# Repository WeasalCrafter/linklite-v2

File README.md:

<!-- PROJECT LOGO -->
<br />
<div align="center">

  <h3 align="center">LinkLite v2</h3>

  <p align="center">
    A modular ESP32-C6 based room light that syncs brightness via ESP-NOW
    <br />
    <a href="https://www.loganfick.com/projects/linklite-v2">See my post on my Website</a><!--
    &middot;
    <a href="#">Project video on Youtube</a>-->
  </p>
</div>

<!-- TABLE OF CONTENTS -->
<details opeb>
  <summary>Table of Contents</summary>
  <ol>
    <li>
      <a href="#files">File Structure</a>
    <li><a href="#contact">Contact</a></li>
    <li><a href="#acknowledgments">Acknowledgments</a></li>
    <li><a href="#license">License</a></li>
  </ol>
</details>

<!-- ABOUT THE PROJECT -->
## About The Project

My dorm room lights are terrible in college, so I decided to make my own. LinkLite is the idea of a modular lighting system that lives locally and not in the cloud while allowing for wireless control and syncing. 

This is the second version of LinkLite, completely redesigned. This time with a custom PCB and much increased brightness.

### Built With

These are the major libraries I used in the programming in the project:

* RotaryEncoder
* Preferences
* ESP-NOW

<!-- CONTACT -->
## Files

The PCB project files can be found under ```kicad/linklite_v2```

```
linklite-v2
├── data
├── kicad
│   └── linklite_v2
├── linklite-bar
├── linklite-controller
├── temperature_logger
├── README.md
├── CLAUDE.md
└── LICENSE.txt
```

The arduino sketches for the ```linklite-bar```, ```linklite-controller```, and ```temperature_logger``` can be found under their respective folders, and my data collected can be found in the ```data``` folder along with the MATLAB script for plot generation.

<!-- CONTACT -->
## Contact

Logan Fick -  loganfickcontact@gmail.com

Project Link: [https://github.com/weasalcrafter/linklite-v2](https://github.com/weasalcrafter/linklite-v2)

Website: [https://loganfick.com/](https://loganfick.com/)

<!-- ACKNOWLEDGMENTS -->
## Acknowledgments
These are the tools I used for this project for designing the schematic, PCB layout, and programming.

* [Claude Code](https://www.claude.ai)
* [KiCad 10.0](https://www.kicad.org/)
* [Digikey Tools](https://www.digikey.com/en/resources/online-conversion-calculators)
* [MATLAB](https://www.mathworks.com/products/matlab.html)

## License

This project is licensed under the MIT License - see the [LICENSE](LICENSE.txt) file for details.

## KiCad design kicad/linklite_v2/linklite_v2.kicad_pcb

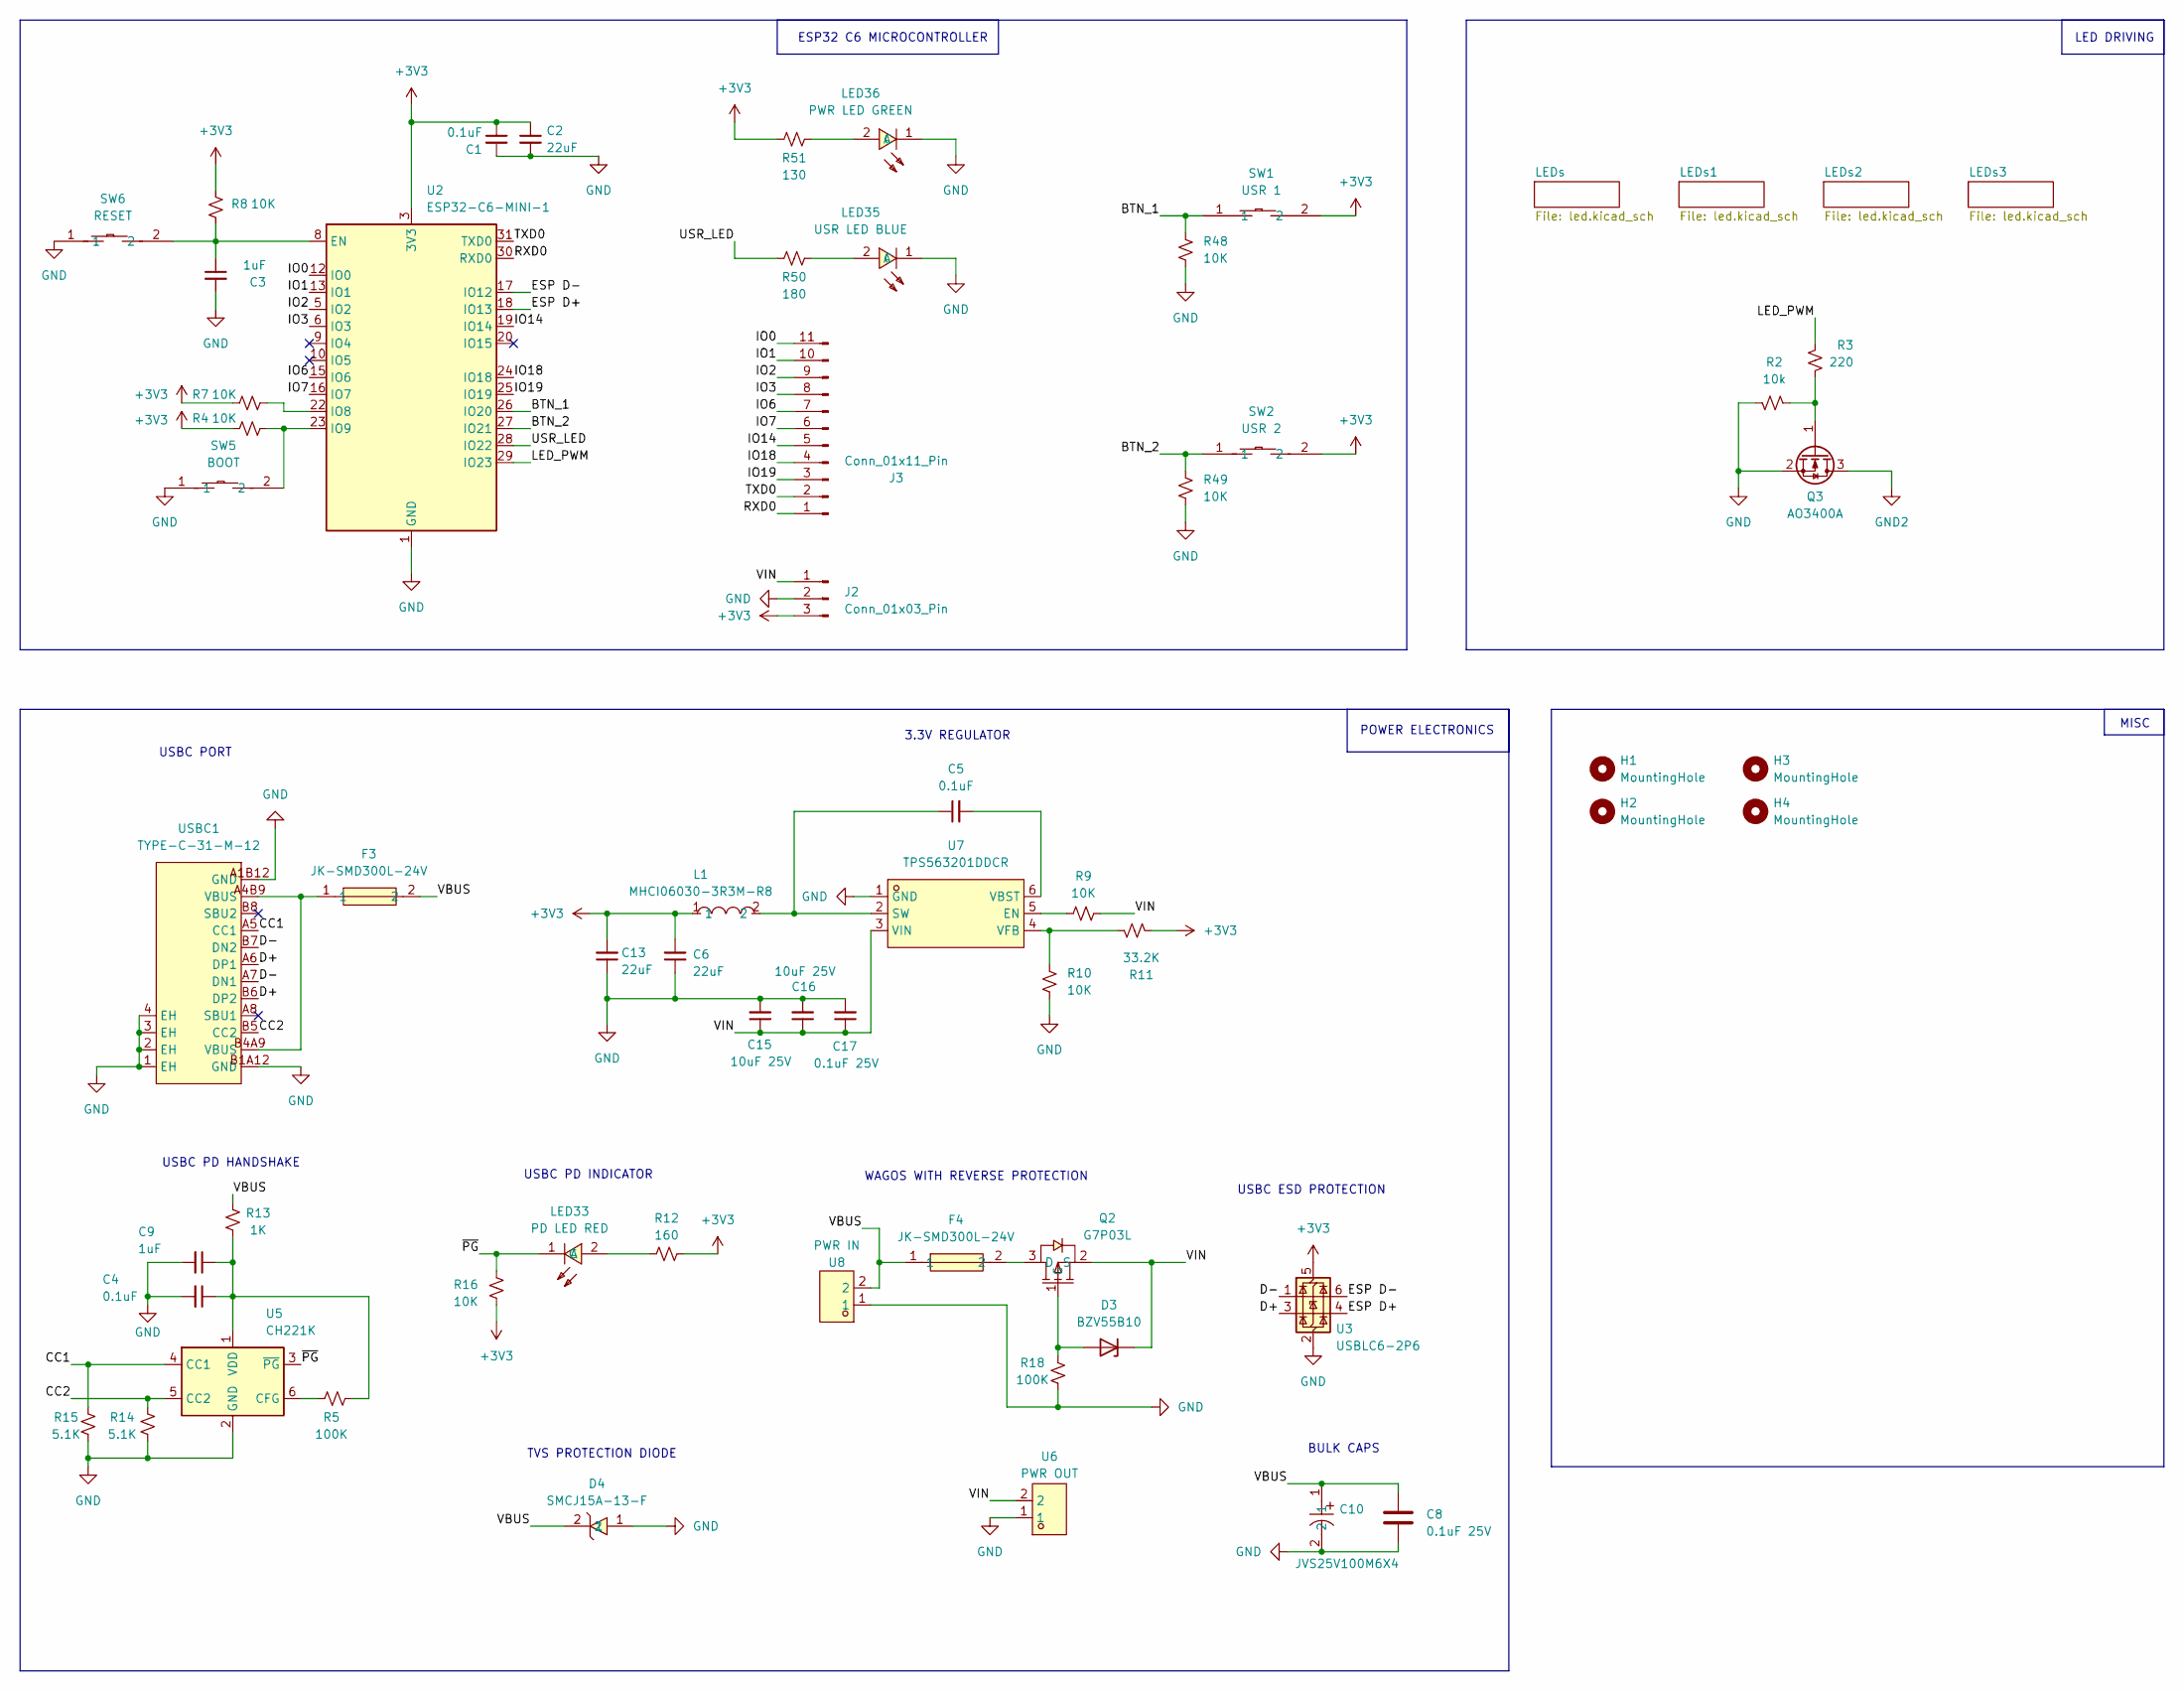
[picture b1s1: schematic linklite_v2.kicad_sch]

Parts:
C1, C4, C5: 0.1uF; C_0603_1608Metric
C2: 22uF; C_0603_1608Metric
C3, C9: 1uF; C_0603_1608Metric
C6, C13: 22uF; C_0805_2012Metric
C8: 0.1uF 25V; C_0805_2012Metric
C10: JVS25V100M6X4; CAP-SMD_BD6.3-L6.6-W6.6-LS7.3-FD_JVS25V100M6X4; MPN JVS25V100M6X4; LCSC Part C51953404
C15, C16: 10uF 25V; C_0805_2012Metric
C17: 0.1uF 25V; C_0603_1608Metric
D3: BZV55B10; D_MiniMELF
D4: SMCJ15A-13-F; SMC_L7.1-W6.2-LS8.1-FD; MPN SMCJ15A-13-F; LCSC Part C135138
F3, F4: JK-SMD300L-24V; F2920; MPN JK-SMD300L-24V; LCSC Part C841188
H1, H2, H3, H4: MountingHole; MountingHole_3.2mm_M3_Pad_TopBottom
J2: Conn_01x03_Pin; PinHeader_1x03_P2.54mm_Horizontal
J3: Conn_01x11_Pin; PinHeader_1x11_P2.54mm_Horizontal
L1: MHCI06030-3R3M-R8; IND-SMD_L7.3-W6.6; MPN MHCI06030-3R3M-R8; LCSC Part C108294
LED33: PD LED RED; LED0603-RD_RED; MPN BL-HUB36G-AV-TRB; LCSC Part C94743
LED35: USR LED BLUE; LED0603-RD_RED; MPN BL-HUB36G-AV-TRB; LCSC Part C481916
LED36: PWR LED GREEN; LED0603-RD_RED; MPN BL-HUB36G-AV-TRB; LCSC Part C84267
Q2: G7P03L; SOT-23-3_L2.9-W1.6-P1.90-LS2.8-BR; MPN G7P03L; LCSC Part C840062
Q3: AO3400A; SOT-23
R2: 10k; R_0603_1608Metric
R3: 220; R_0603_1608Metric
R4, R7, R8, R9, R10, R16, R48, R49: 10K; R_0603_1608Metric
R5, R18: 100K; R_0603_1608Metric
R11: 33.2K; R_0603_1608Metric
R12: 160; R_0603_1608Metric
R13: 1K; R_0603_1608Metric
R14, R15: 5.1K; R_0603_1608Metric
R50: 180; R_0603_1608Metric
R51: 130; R_0603_1608Metric
SW1: USR 1; KEY-SMD_B3U-1000PM; MPN B3U-1000P; LCSC Part C231329
SW2: USR 2; KEY-SMD_B3U-1000PM; MPN B3U-1000P; LCSC Part C231329
SW5: BOOT; KEY-SMD_B3U-1000PM; MPN B3U-1000P; LCSC Part C231329
SW6: RESET; KEY-SMD_B3U-1000PM; MPN B3U-1000P; LCSC Part C231329
U2: ESP32-C6-MINI-1; LCSC Part C5736265
U3: USBLC6-2P6; SOT-666
U5: CH221K; SOT-23-6
U6: PWR OUT; CONN-SMD_2060-452; MPN 2060-452/998-404; LCSC Part C2765055
U7: TPS563201DDCR; SOT-23-6_L2.9-W1.6-P0.95-LS2.8-BR; MPN TPS563201DDCR; LCSC Part C116592
U8: PWR IN; CONN-SMD_2060-452; MPN 2060-452/998-404; LCSC Part C2765055
USBC1: TYPE-C-31-M-12; USB-C_SMD-TYPE-C-31-M-12_1; LCSC Part C165948

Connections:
+3V3: C1.1, C2.1, C6.2, C13.2, J2.3, L1.1, R4.1, R7.1, R8.1, R11.2, R12.2, R16.1, R51.1, SW1.2, SW2.2, U2.3 (3V3), U3.5 (VBUS); also elsewhere on the board
/BTN_1: R48.1, SW1.1, U2.26 (IO20)
/BTN_2: R49.1, SW2.1, U2.27 (IO21)
/CC1: R15.2, U5.4 (CC1), USBC1.A5 (CC1)
/CC2: R14.2, U5.5 (CC2), USBC1.B5 (CC2)
/D+: U3.3 (I/O2), USBC1.A6 (DP1), USBC1.B6 (DP2)
/D-: U3.1 (I/O1), USBC1.A7 (DN1), USBC1.B7 (DN2)
/ESP D+: U2.18 (IO13), U3.4 (I/O2)
/ESP D-: U2.17 (IO12), U3.6 (I/O1)
/IO0: J3.11, U2.12 (IO0)
/IO1: J3.10, U2.13 (IO1)
/IO2: J3.9, U2.5 (IO2)
/IO3: J3.8, U2.6 (IO3)
/IO6: J3.7, U2.15 (IO6)
/IO7: J3.6, U2.16 (IO7)
/IO14: J3.5, U2.19 (IO14)
/IO18: J3.4, U2.24 (IO18)
/IO19: J3.3, U2.25 (IO19)
/LED_PWM: R3.1, U2.29 (IO23)
/RXD0: J3.1, U2.30 (RXD0)
/TXD0: J3.2, U2.31 (TXD0)
/USR_LED: R50.1, U2.28 (IO22)
/VBUS: C8.1, C10.1, D4.2, F3.2, F4.1, R13.2, U8.2
/VIN: C15.1, C16.1, C17.1, D3.1 (K), J2.1, Q2.2 (S), R9.2, U6.2, U7.3 (VIN)
/~PG: LED33.1 (C), R16.2, U5.3 (~PG)
GND: C1.2, C2.2, C3.2, C4.2, C6.1, C8.2, C9.2, C10.2, C13.1, C15.2, C16.2, C17.2, D4.1, J2.2, LED35.1 (C), LED36.1 (C), Q3.2 (S), R2.1, R10.1, R14.1, R15.1, R18.1, R48.2, R49.2, SW5.1, SW6.1, U2.1 (GND), U2.2 (GND), U2.11 (GND), U2.14 (GND), U2.36 (GND), U2.37 (GND), U2.38 (GND), U2.39 (GND), U2.40 (GND), U2.41 (GND), U2.42 (GND), U2.43 (GND), U2.44 (GND), U2.45 (GND), U2.46 (GND), U2.47 (GND), U2.48 (GND), U2.49 (GND), U2.50 (GND), U2.51 (GND), U2.52 (GND), U2.53 (GND), U3.2 (GND), U5.2 (GND), U6.1, U7.1 (GND), U8.1, USBC1.1 (EH), USBC1.2 (EH), USBC1.3 (EH), USBC1.4 (EH), USBC1.A1B12 (GND), USBC1.B1A12 (GND)
GND2: Q3.3 (D); also elsewhere on the board
unnamed: D3.2 (A), Q2.1 (G), R18.2
unnamed: F3.1, USBC1.A4B9 (VBUS), USBC1.B4A9 (VBUS)
unnamed: LED33.2 (A), R12.1
unnamed: LED35.2 (A), R50.2
unnamed: LED36.2 (A), R51.2
unnamed: F4.2, Q2.3 (D)
unnamed: Q3.1 (G), R2.2, R3.2
unnamed: C3.1, R8.2, SW6.2, U2.8 (EN)
unnamed: R7.2, U2.22 (IO8)
unnamed: R4.2, SW5.2, U2.23 (IO9)
unnamed: R5.1, U5.6 (CFG)
unnamed: C4.1, C9.1, R5.2, R13.1, U5.1 (VDD)
unnamed: R9.1, U7.5 (EN)
unnamed: C5.1, L1.2, U7.2 (SW)
unnamed: C5.2, U7.6 (VBST)
unnamed: R10.2, R11.1, U7.4 (VFB)

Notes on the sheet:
USBC ESD PROTECTION
ESP32 C6 MICROCONTROLLER
BULK CAPS
USBC PD INDICATOR
USBC PORT
USBC PD HANDSHAKE
WAGOS WITH REVERSE PROTECTION
MISC
3.3V REGULATOR
LED DRIVING
TVS PROTECTION DIODE
POWER ELECTRONICS

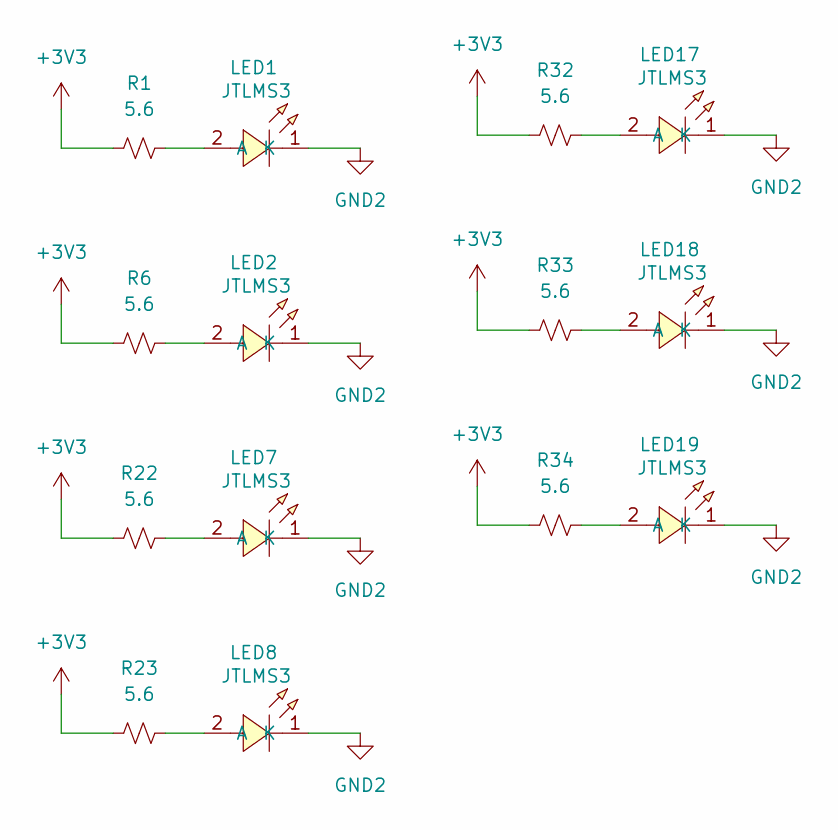
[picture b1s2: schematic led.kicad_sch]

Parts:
LED1, LED2, LED7, LED8, LED17, LED18, LED19: JTLMS3; LED-SMD_L3.5-W2.8-FD-2835_WHITE; MPN GW JTLMS3.GM-G4G8-XX57-1-60-R33; LCSC Part C34162565
R1, R6, R22, R23, R32, R33, R34: 5.6; R_0603_1608Metric; LCSC Part C325756

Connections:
+3V3: R1.2, R6.2, R22.2, R23.2, R32.2, R33.2, R34.2; also elsewhere on the board
GND2: LED1.1 (K), LED2.1 (K), LED7.1 (K), LED8.1 (K), LED17.1 (K), LED18.1 (K), LED19.1 (K); also elsewhere on the board
unnamed: LED1.2 (A), R1.1
unnamed: LED2.2 (A), R6.1
unnamed: LED7.2 (A), R22.1
unnamed: LED8.2 (A), R23.1
unnamed: LED17.2 (A), R32.1
unnamed: LED18.2 (A), R33.1
unnamed: LED19.2 (A), R34.1

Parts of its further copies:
LED3, LED4, LED5, LED6, LED9, LED10, LED11, LED12, LED13, LED14, LED15, LED16, LED21, LED22, LED23, LED25, LED26, LED27, LED29, LED30, LED31: JTLMS3; LED-SMD_L3.5-W2.8-FD-2835_WHITE; MPN GW JTLMS3.GM-G4G8-XX57-1-60-R33; LCSC Part C34162565
R17, R19, R20, R21, R24, R25, R26, R27, R28, R29, R30, R31, R36, R37, R38, R40, R41, R42, R44, R45, R46: 5.6; R_0603_1608Metric; LCSC Part C325756

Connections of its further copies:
+3V3: R17.2, R19.2, R20.2, R21.2, R24.2, R25.2, R26.2, R27.2, R28.2, R29.2, R30.2, R31.2, R36.2, R37.2, R38.2, R40.2, R41.2, R42.2, R44.2, R45.2, R46.2; also elsewhere on the board
GND2: LED3.1 (K), LED4.1 (K), LED5.1 (K), LED6.1 (K), LED9.1 (K), LED10.1 (K), LED11.1 (K), LED12.1 (K), LED13.1 (K), LED14.1 (K), LED15.1 (K), LED16.1 (K), LED21.1 (K), LED22.1 (K), LED23.1 (K), LED25.1 (K), LED26.1 (K), LED27.1 (K), LED29.1 (K), LED30.1 (K), LED31.1 (K); also elsewhere on the board
unnamed: LED3.2 (A), R17.1
unnamed: LED4.2 (A), R19.1
unnamed: LED5.2 (A), R20.1
unnamed: LED6.2 (A), R21.1
unnamed: LED9.2 (A), R24.1
unnamed: LED10.2 (A), R25.1
unnamed: LED11.2 (A), R26.1
unnamed: LED12.2 (A), R27.1
unnamed: LED13.2 (A), R28.1
unnamed: LED14.2 (A), R29.1
unnamed: LED15.2 (A), R30.1
unnamed: LED16.2 (A), R31.1
unnamed: LED21.2 (A), R36.1
unnamed: LED22.2 (A), R37.1
unnamed: LED23.2 (A), R38.1
unnamed: LED25.2 (A), R40.1
unnamed: LED26.2 (A), R41.1
unnamed: LED27.2 (A), R42.1
unnamed: LED29.2 (A), R44.1
unnamed: LED30.2 (A), R45.1
unnamed: LED31.2 (A), R46.1

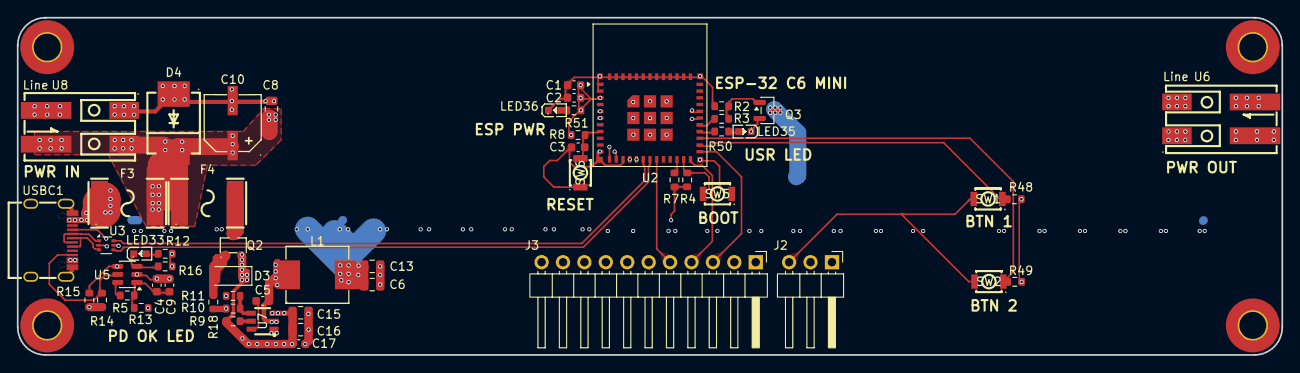
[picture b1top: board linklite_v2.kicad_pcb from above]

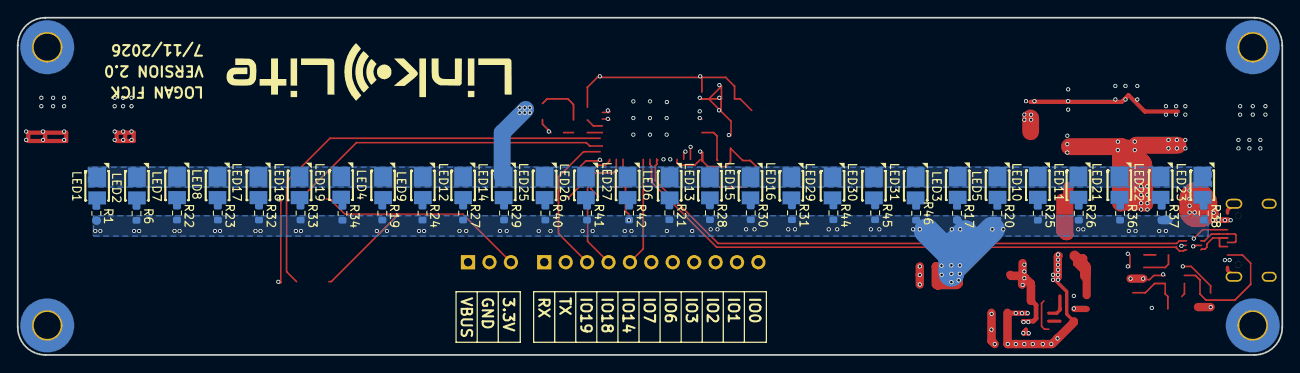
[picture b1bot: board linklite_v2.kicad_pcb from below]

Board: 4 copper layers, 150.0 x 40.0 mm, 115 parts (56 on the bottom side), 71 nets.

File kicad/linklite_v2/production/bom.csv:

Designator,Footprint,Quantity,Value,LCSC Part #
"C1, C4, C5",0603,3,0.1uF,
C10,CAP-SMD_BD6.3-L6.6-W6.6-LS7.3-FD_JVS25V100M6X4,1,JVS25V100M6X4,C51953404
"C13, C6",0805,2,22uF,
"C15, C16",0805,2,10uF 25V,
C17,0603,1,0.1uF 25V,
C2,0603,1,22uF,
"C3, C9",0603,2,1uF,
C8,0805,1,0.1uF 25V,
D3,D_MiniMELF,1,BZV55B10,
D4,SMC_L7.1-W6.2-LS8.1-FD,1,SMCJ15A-13-F,C135138
"F3, F4",F2920,2,JK-SMD300L-24V,C841188
J2,PinHeader_1x03_P2.54mm_Horizontal,1,Conn_01x03_Pin,
J3,PinHeader_1x11_P2.54mm_Horizontal,1,Conn_01x11_Pin,
L1,IND-SMD_L7.3-W6.6,1,MHCI06030-3R3M-R8,C108294
"LED1, LED10, LED11, LED12, LED13, LED14, LED15, LED16, LED17, LED18, LED19, LED2, LED21, LED22, LED23, LED25, LED26, LED27, LED29, LED3, LED30, LED31, LED4, LED5, LED6, LED7, LED8, LED9",LED-SMD_L3.5-W2.8-FD-2835_WHITE,28,JTLMS3,C34162565
LED33,LED0603-RD_RED,1,PD LED RED,C94743
LED35,LED0603-RD_RED,1,USR LED BLUE,C481916
LED36,LED0603-RD_RED,1,PWR LED GREEN,C84267
Q2,SOT-23-3_L2.9-W1.6-P1.90-LS2.8-BR,1,G7P03L,C840062
Q3,SOT-23,1,AO3400A,
"R1, R17, R19, R20, R21, R22, R23, R24, R25, R26, R27, R28, R29, R30, R31, R32, R33, R34, R36, R37, R38, R40, R41, R42, R44, R45, R46, R6",0603,28,5.6, C325756 
"R10, R16, R2, R4, R48, R49, R7, R8, R9",0603,9,10K,
R11,0603,1,33.2K,
R12,0603,1,160,
R13,0603,1,1K,
"R14, R15",0603,2,5.1K,
"R18, R5",0603,2,100K,
R3,0603,1,220,
R50,0603,1,180,
R51,0603,1,130,
SW3,SW-SMD_4P-L3.5-W3.0-P1.50-LS4.7,1,RESET,C51927445
SW4,SW-SMD_4P-L3.5-W3.0-P1.50-LS4.7,1,BOOT,C51927445
"SW5, SW6",SW-SMD_4P-L3.5-W3.0-P1.50-LS4.7,2,USR 1,C51927445
U2,ESP32-C6-MINI-1,1,ESP32-C6-MINI-1,C5736265
U3,SOT-666,1,USBLC6-2P6,
U5,SOT-23-6,1,CH221K,
U6,CONN-SMD_2060-452,1,PWR OUT,C2765055
U7,SOT-23-6_L2.9-W1.6-P0.95-LS2.8-BR,1,TPS563201DDCR,C116592
U8,CONN-SMD_2060-452,1,PWR IN,C2765055
USBC1,USB-C_SMD-TYPE-C-31-M-12_1,1,TYPE-C-31-M-12,C165948
